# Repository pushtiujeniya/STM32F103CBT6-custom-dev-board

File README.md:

# **STM32F103 custom development board**

This project contains custom development board based on the STM32F103 microcontroller.This baord created using kicad 9.0 software with proper routing , signal integrity, differential pair routing of USB connection.

## **Features**
- STM32F103 microcontroller
- Onboard 3.3V linear voltage regulator(AMS1117-3.3)
- Onboard Led indication on 3.3V power supply
- Micro USB interface for power and communication
- SWD interfacae for debugging and programming
- UART and I2C breakout headers
- Decoupling capacitors placed for stable operation
- External crystal oscillator with load capacitors
- MCU reser switch
- Clean PCB layout with proper grouding and differential routing for mico USB connection
- Board size: 35.5 mm X 23.6 mm

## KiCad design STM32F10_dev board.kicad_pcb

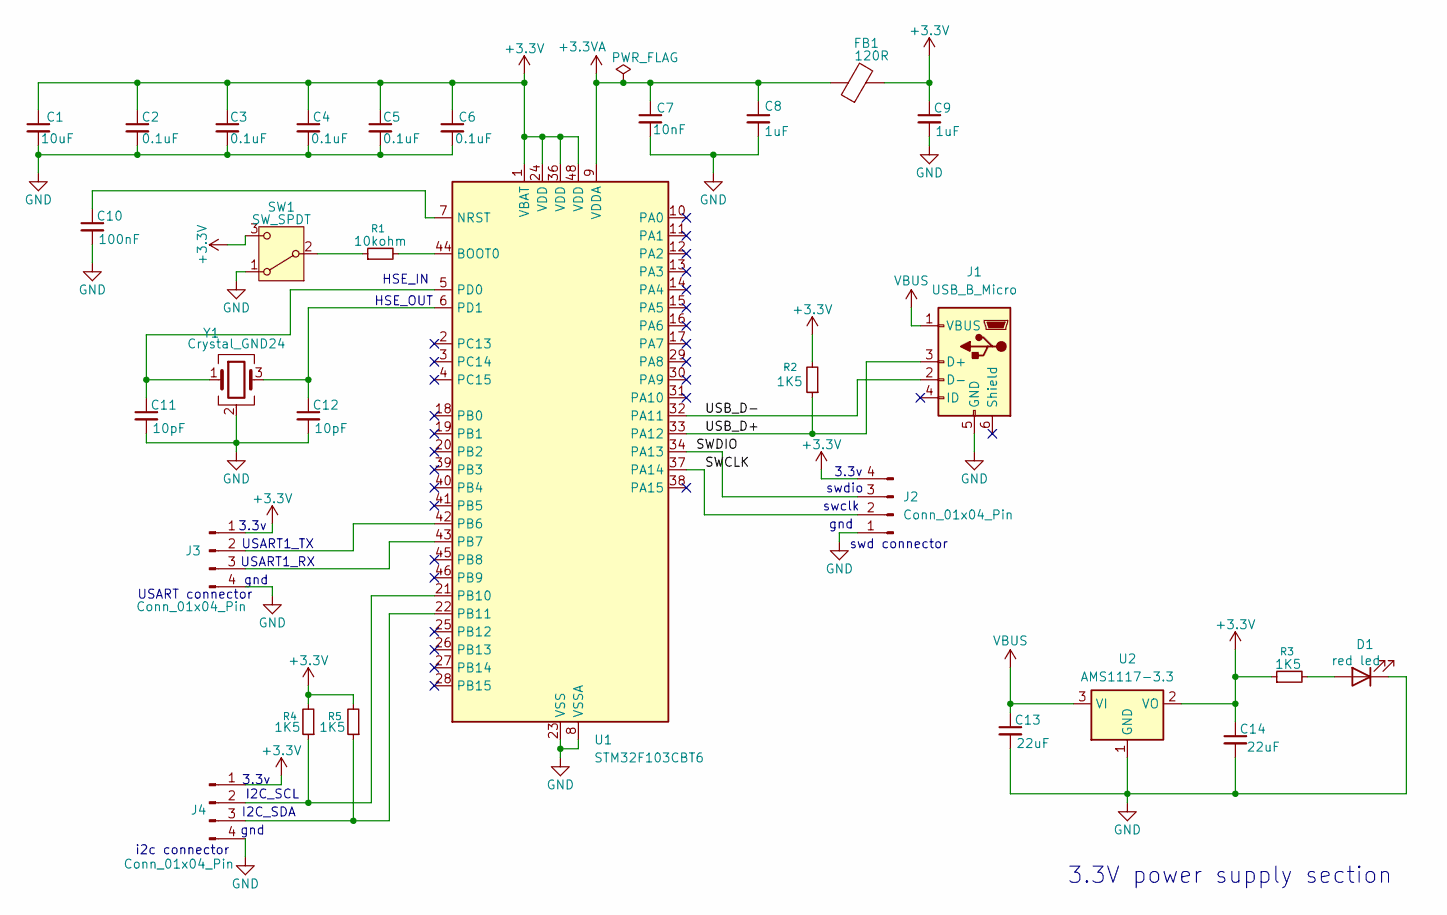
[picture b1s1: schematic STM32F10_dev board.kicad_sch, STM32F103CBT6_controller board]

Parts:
C1: 10uF; C_0603_1608Metric
C2, C3, C4, C5, C6: 0.1uF; C_0402_1005Metric
C7: 10nF; C_0402_1005Metric
C8, C9: 1uF; C_0402_1005Metric
C10: 100nF; C_0402_1005Metric
C11, C12: 10pF; C_0402_1005Metric
C13, C14: 22uF; C_0805_2012Metric
D1: red led; LED_0603_1608Metric
FB1: 120R; L_0603_1608Metric
J1: USB_B_Micro; USB_Micro-B_Wuerth_629105150521
J2, J3, J4: Conn_01x04_Pin; PinHeader_1x04_P2.54mm_Vertical
R1: 10kohm; R_0402_1005Metric
R2, R3, R4, R5: 1K5; R_0402_1005Metric
SW1: SW_SPDT; SW_SPDT_PCM12
U1: STM32F103CBT6; LQFP-48_7x7mm_P0.5mm
U2: AMS1117-3.3; SOT-223-3_TabPin2
Y1: Crystal_GND24; Crystal_SMD_3225-4Pin_3.2x2.5mm

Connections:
+3.3V: C1.1, C2.1, C3.1, C4.1, C5.1, C6.1, C9.1, C14.1, FB1.2, J2.4, J3.1, J4.1, R2.2, R3.1, R4.2, R5.2, SW1.3 (C), U1.1 (VBAT), U1.24 (VDD), U1.36 (VDD), U1.48 (VDD), U2.2 (VO)
+3.3VA: C7.1, C8.1, FB1.1, U1.9 (VDDA)
/SWCLK: J2.2, U1.37 (PA14)
/SWDIO: J2.3, U1.34 (PA13)
/USB_D+: J1.3 (D+), R2.1, U1.33 (PA12)
/USB_D-: J1.2 (D-), U1.32 (PA11)
GND: C1.2, C2.2, C3.2, C4.2, C5.2, C6.2, C7.2, C8.2, C9.2, C10.2, C11.2, C12.2, C13.2, C14.2, D1.1 (K), J1.5 (GND), J2.1, J3.4, J4.4, SW1.1 (A), U1.8 (VSSA), U1.23 (VSS), U1.35 (VSS), U1.47 (VSS), U2.1 (GND), Y1.2 (G), Y1.4 (G)
unnamed: D1.2 (A), R3.2
unnamed: J3.2, U1.42 (PB6)
unnamed: J3.3, U1.43 (PB7)
unnamed: J4.2, R4.1, U1.21 (PB10)
unnamed: J4.3, R5.1, U1.22 (PB11)
unnamed: R1.1, SW1.2 (B)
unnamed: R1.2, U1.44 (BOOT0)
unnamed: C10.1, U1.7 (NRST)
unnamed: C11.1, U1.5 (PD0), Y1.1
unnamed: C12.1, U1.6 (PD1), Y1.3
VBUS: C13.1, J1.1 (VBUS), U2.3 (VI)

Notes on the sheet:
USART1_RX
swclk
3.3v
3.3v
i2c connector
swd connector
USART connector
swdio
HSE_OUT
3.3V power supply section
HSE_IN
gnd
USART1_TX
I2C_SCL
gnd
I2C_SDA

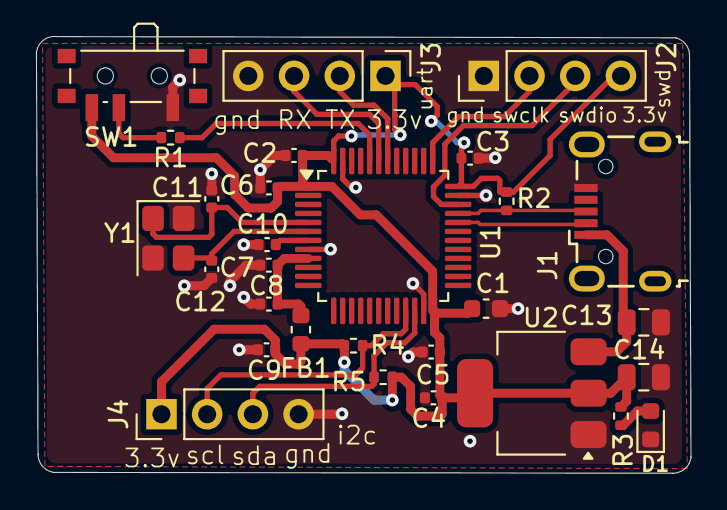
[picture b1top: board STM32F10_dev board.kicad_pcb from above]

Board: 2 copper layers, 36.4 x 24.3 mm, 29 parts (0 on the bottom side), 18 nets.

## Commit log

2026-04-14 Add temporary file in 3D_view directory
2026-04-15 Add README for STM32F103 custom development board
    Added project description and features for STM32F103 board.
2026-04-15 Update README with additional features
    Added features and details about the STM32F103 development board.
2026-04-15 3D view images added
2026-04-15 layout files added
2026-04-15 schematic files added
2026-04-15 project files added
2026-04-15 Add temp file to Backup folder
2026-04-16 back up files added
2026-04-16 Add temporary file in External library directory
2026-04-16 micro USB step file(3D model)
2026-04-16 Add board size information to README
2026-05-04 Document file added
